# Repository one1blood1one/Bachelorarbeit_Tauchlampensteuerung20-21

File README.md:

Dieses Repository gehört zur Bachelorarbeit von Dennis Sitnic. 
Es enthält (nach der Fertigstellung) folgende Dateien:

**Unterlagen:**
- Bachelorarbeit PDF
- Präsentation der Arbeit
- Gebrauchsanleitung 

**Breakoutboard:**
- Eagle Daten
- Gerberdaten
- BOM

**Gesamtschaltung:**
- Eagle Daten
- Gerberdaten
- BOM

**Software:**
- Microcontroller Code
- Initialprogrammierung shell script

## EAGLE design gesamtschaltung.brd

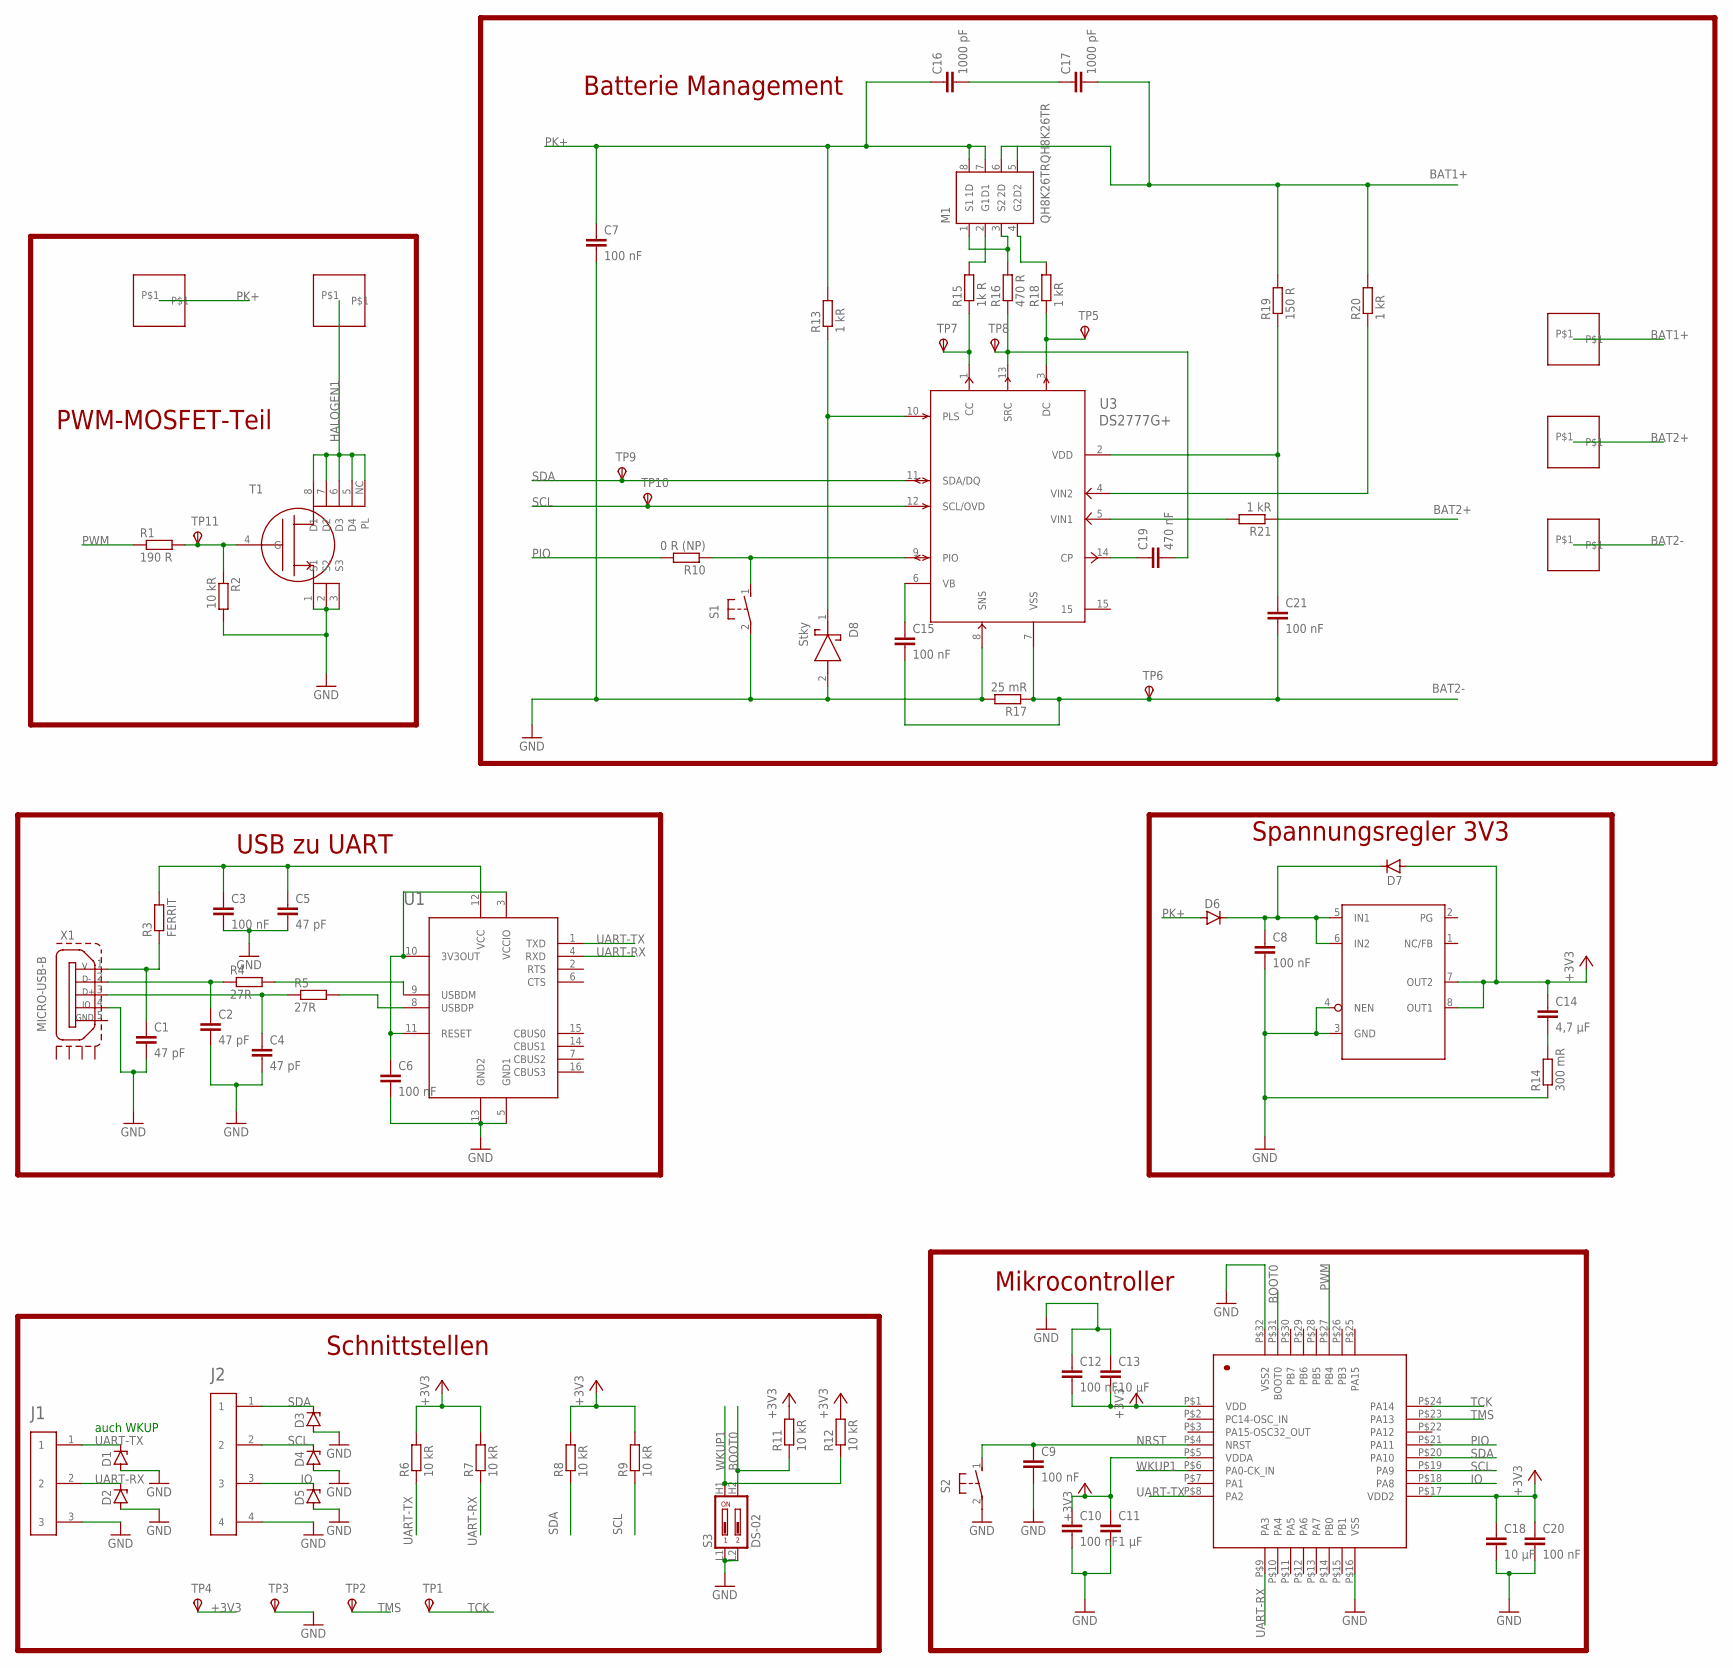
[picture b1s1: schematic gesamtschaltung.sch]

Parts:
C1, C2, C4, C5: 47 pF; C0603
C3, C6, C7, C8, C9, C10, C12, C15, C20, C21: 100 nF; C0603
C11: 1 µF; C0603
C13, C18: 10 µF; C0603
C14: 4,7 µF; C0603
C16, C17: 1000 pF; C0603
C19: 470 nF; C0603
D1, D2, D3, D4, D5: TVS-3V5; TVS-FOOT
D6, D7: DIODE-SILIZIUM; TVS-FOOT
D8: Stky; SOD3715X135N
J1: 3PIN; HDRV3W64P254_1X3_762X254X854B
J2: 4PIN-MALE; 4P-MALE-FOOT
M1: QH8K26TRQH8K26TR; SOTFL65P280X85-8N
MC1: STM32L031K6T6; LQFP32
P1, P2, P3, P4, P5: PAD-3MM
R1: 190 R; R0603
R2, R6, R7, R8, R9, R11, R12: 10 kR; R0603
R3: FERRIT; R0603
R4, R5: 27R; R0603
R10: 0 R (NP); R0603
R13, R18, R20, R21: 1 kR; R0603
R14: 300 mR; R0603
R15: 1k R; R0603
R16: 470 R; R0603
R17: 25 mR; R0603
R19: 150 R; R0603
S1, S2: BUTTON
S3: DS-02
T1: POWER-MOS; SO-8
TP1, TP2, TP3, TP4: TPSTP20R; TP20R
TP5, TP6, TP7, TP8, TP9, TP10, TP11: TPSTP10R; TP10R
U1: FT230X; SSOP16
U2: TPS76633DR; TPS766FOOTPRINT
U3: DS2777G+; DS2777_TDFN-15-OWN
X1: MICRO-USB-B; MICROUSBFOOT

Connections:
+3V3: C10.1, C11.1, C12.2, C13.2, C14.1, C18.1, C20.1, D7.A, MC1.P$1 (VDD), MC1.P$5 (VDDA), MC1.P$17 (VDD2), R6.2, R7.2, R8.2, R9.2, R11.2, R12.2, TP4.TP, U2.7 (OUT2), U2.8 (OUT1)
BAT1+: C17.2, M1.5 (D2), M1.6 (2D), P3.P$1, R19.2, R20.2
BAT2+: P4.P$1, R21.1
BAT2-: C15.2, C21.2, P5.P$1, R17.1, TP6.TP, U3.7 (VSS)
BOOT0: MC1.P$31 (BOOT0), R11.1, S3.H2
GND: C1.2, C2.2, C3.2, C4.2, C5.2, C6.2, C7.2, C8.2, C9.2, C10.2, C11.2, C12.1, C13.1, C18.2, C20.2, D1.A, D2.A, D3.A, D4.A, D5.A, D8.2 (A), J1.3, J2.4, MC1.P$16 (VSS), MC1.P$32 (VSS2), R2.2, R14.1, R17.2, S1.2 (L), S2.2 (L), S3.L1, S3.L2, T1.1 (S1), T1.2 (S2), T1.3 (S3), TP3.TP, U1.5 (GND1), U1.13 (GND2), U2.3 (GND), U2.4 (NEN), U3.8 (SNS), X1.4 (IO)
HALOGEN1: P2.P$1, T1.5 (D4), T1.6 (D3), T1.7 (D2), T1.8 (D1), T1.NC (PL)
IO: D5.K, J2.3, MC1.P$18 (PA8)
unnamed: R21.2, U3.5 (VIN1)
unnamed: R20.1, U3.4 (VIN2)
unnamed: C21.1, R19.1, U3.2 (VDD)
unnamed: C3.1, C5.1, R3.2, U1.12 (VCC)
unnamed: R1.2, R2.1, T1.4 (G), TP11.TP
unnamed: R4.2, U1.9 (USBDM)
unnamed: R15.1, TP7.TP, U3.1 (CC)
unnamed: C19.2, R16.1, TP8.TP, U3.13 (SRC)
unnamed: R18.1, TP5.TP, U3.3 (DC)
unnamed: M1.2 (G1), R15.2
unnamed: M1.4 (G2), R18.2
unnamed: M1.1 (S1), M1.3 (S2), R16.2
unnamed: C15.1, U3.6 (VB)
unnamed: C4.1, R5.1, X1.3 (D+)
unnamed: C16.2, C17.1
unnamed: C19.1, U3.14 (CP)
unnamed: D8.1 (K), R13.1, U3.10 (PLS)
unnamed: C8.1, D6.K, D7.K, U2.5 (IN1), U2.6 (IN2)
unnamed: C2.1, R4.1, X1.2 (D-)
unnamed: C14.2, R14.2
unnamed: R5.2, U1.8 (USBDP)
unnamed: C6.1, U1.3 (VCCIO), U1.10 (3V3OUT), U1.11 (RESET)
unnamed: C1.1, R3.1, X1.1 (V)
NRST: C9.1, MC1.P$4 (NRST), S2.1 (H)
PIO: MC1.P$21 (PA11), R10.2
PIO1: R10.1, S1.1 (H), U3.9 (PIO)
PK+: C7.1, C16.1, D6.A, M1.7 (D1), M1.8 (1D), P1.P$1, R13.2
PWM: MC1.P$27 (PB4), R1.1
SCL: D4.K, J2.2, MC1.P$19 (PA9), R9.1, TP10.TP, U3.12 (SCL/OVD)
SDA: D3.K, J2.1, MC1.P$20 (PA10), R8.1, TP9.TP, U3.11 (SDA/DQ)
TCK: MC1.P$24 (PA14), TP1.TP
TMS: MC1.P$23 (PA13), TP2.TP
UART-RX: D2.K, J1.2, MC1.P$9 (PA3), R7.1, U1.4 (RXD)
UART-TX: D1.K, J1.1, MC1.P$8 (PA2), R6.1, U1.1 (TXD)
WKUP1: MC1.P$6 (PA0-CK_IN), R12.1, S3.H1

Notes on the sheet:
auch WKUP
USB zu UART
Mikrocontroller
Spannungsregler 3V3
PWM-MOSFET-Teil
Batterie Management
Schnittstellen

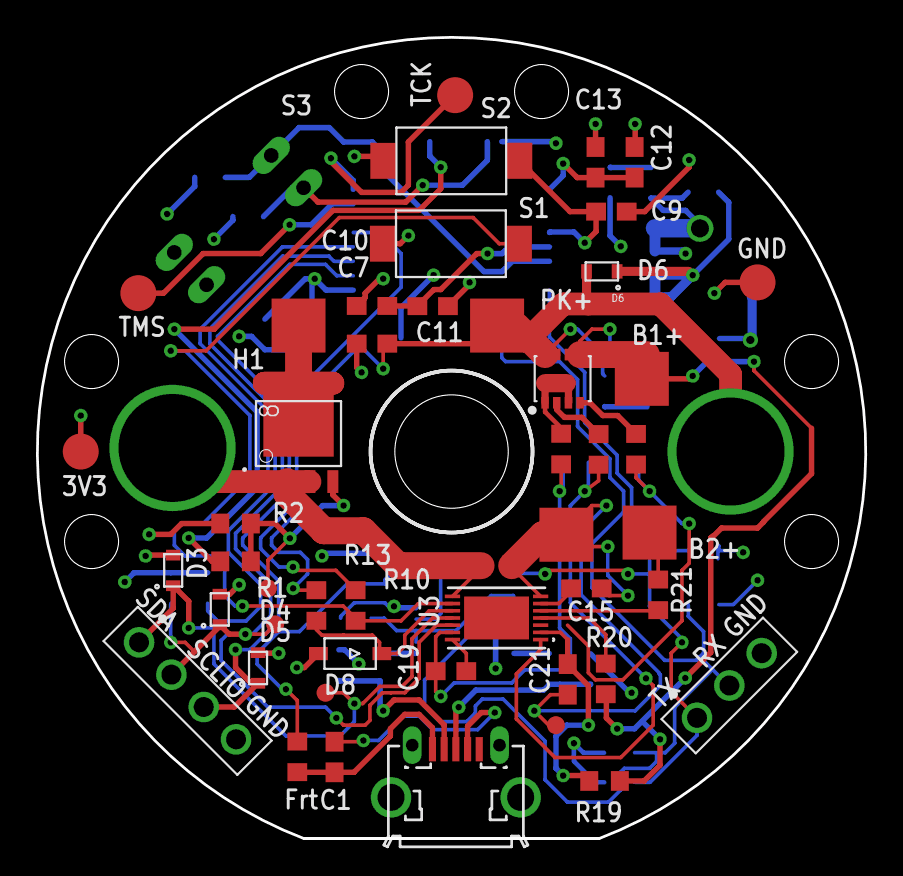
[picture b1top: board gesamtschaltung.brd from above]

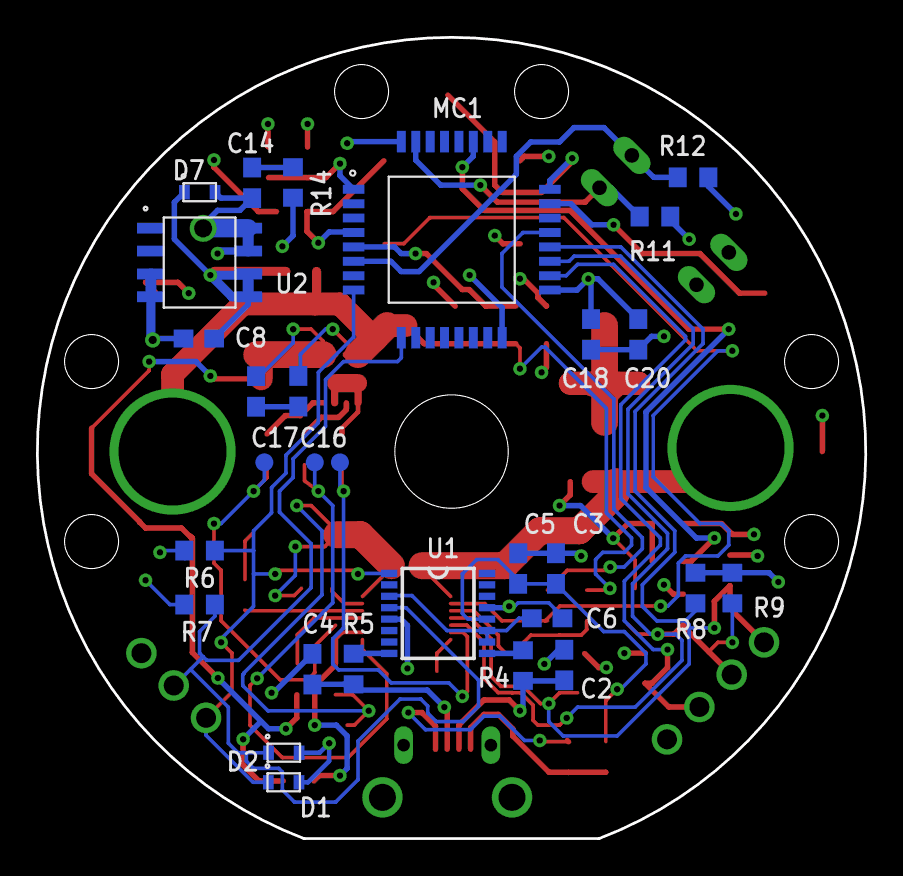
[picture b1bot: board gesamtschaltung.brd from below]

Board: 4 copper layers, 46.0 x 44.5 mm, 78 parts (29 on the bottom side), 43 nets.

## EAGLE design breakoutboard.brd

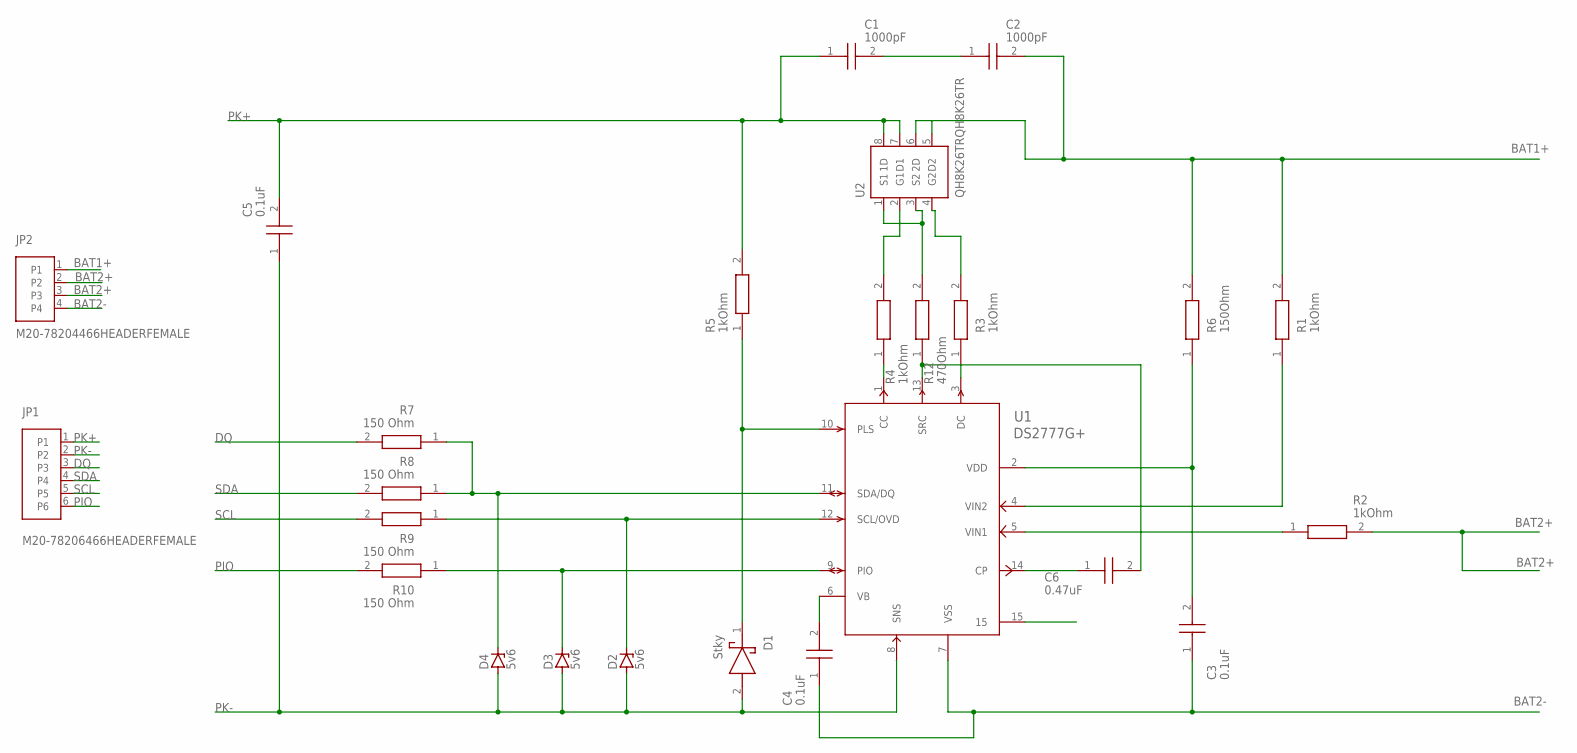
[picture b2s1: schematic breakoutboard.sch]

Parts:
C1, C2: 1000pF; CAPC2012X100N
C3, C4, C5: 0.1uF; CAPC2012X100N
C6: 0.47uF; CAPC2012X100N
D1: Stky; SOD3715X135N
D2, D3, D4: 5v6; SODFL1608X75N
JP1: M20-78206466HEADERFEMALE; HDRVR6W65P254_1X6_1564X250X865B
JP2: M20-78204466HEADERFEMALE; HDRVR4W65P254_1X4_1056X250X865B
R1, R2, R3, R4, R5: 1kOhm; RESC2012X70N
R6: 150Ohm; RESC2012X70N
R7, R8, R9, R10: 150 Ohm; RESC2012X70N
R12: 470Ohm; RESC2012X70N
U1: DS2777G+; DS2777_TDFN-15-OWN
U2: QH8K26TRQH8K26TR; SOTFL65P280X85-8N

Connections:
BAT1+: C2.2, JP2.1, R1.2, R6.2, U2.5 (D2), U2.6 (2D)
BAT2+: JP2.2, JP2.3, R2.2
BAT2-: C3.1, C4.1, JP2.4, U1.7 (VSS), U1.15
DQ: JP1.3, R7.2
unnamed: R2.1, U1.5 (VIN1)
unnamed: R1.1, U1.4 (VIN2)
unnamed: C3.2, R6.1, U1.2 (VDD)
unnamed: R4.1, U1.1 (CC)
unnamed: C6.2, R12.1, U1.13 (SRC)
unnamed: R3.1, U1.3 (DC)
unnamed: R4.2, U2.2 (G1)
unnamed: R3.2, U2.4 (G2)
unnamed: R12.2, U2.1 (S1), U2.3 (S2)
unnamed: C4.2, U1.6 (VB)
unnamed: C1.2, C2.1
unnamed: D4.1 (K), R7.1, R8.1, U1.11 (SDA/DQ)
unnamed: C6.1, U1.14 (CP)
unnamed: D1.1 (K), R5.1, U1.10 (PLS)
unnamed: D2.1 (K), R9.1, U1.12 (SCL/OVD)
unnamed: D3.1 (K), R10.1, U1.9 (PIO)
PIO: JP1.6, R10.2
PK+: C1.1, C5.2, JP1.1, R5.2, U2.7 (D1), U2.8 (1D)
PK-: C5.1, D1.2 (A), D2.2 (A), D3.2 (A), D4.2 (A), JP1.2, U1.8 (SNS)
SCL: JP1.5, R9.2
SDA: JP1.4, R8.2

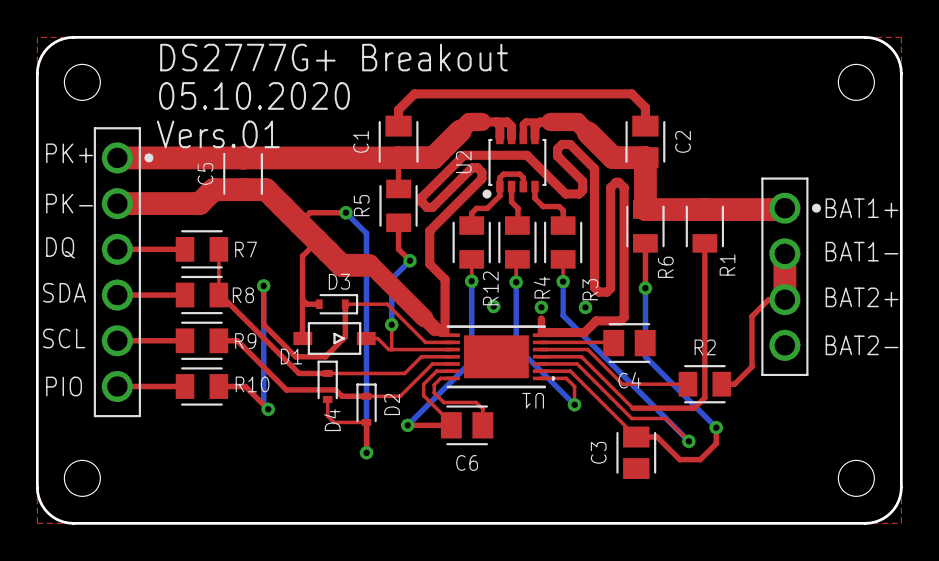
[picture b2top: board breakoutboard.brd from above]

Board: 2 copper layers, 48.0 x 27.0 mm, 25 parts (0 on the bottom side), 25 nets.
